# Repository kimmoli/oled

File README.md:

oled
====

LPC81X micro and OLED module interface.

Fits beneath LM096-128064 oled module.
datasheet e.g. http://s3.electrodragon.com/wp-content/uploads/2012/01/LM096-128064.pdf

Controller datasheet http://www.adafruit.com/datasheets/SSD1306.pdf

Pinheader has pins for I2C and UART0 (TTL) which is also used for ISP.
Supply voltage from 3.5 to 6.0 V (onboard 3.3V LDO)

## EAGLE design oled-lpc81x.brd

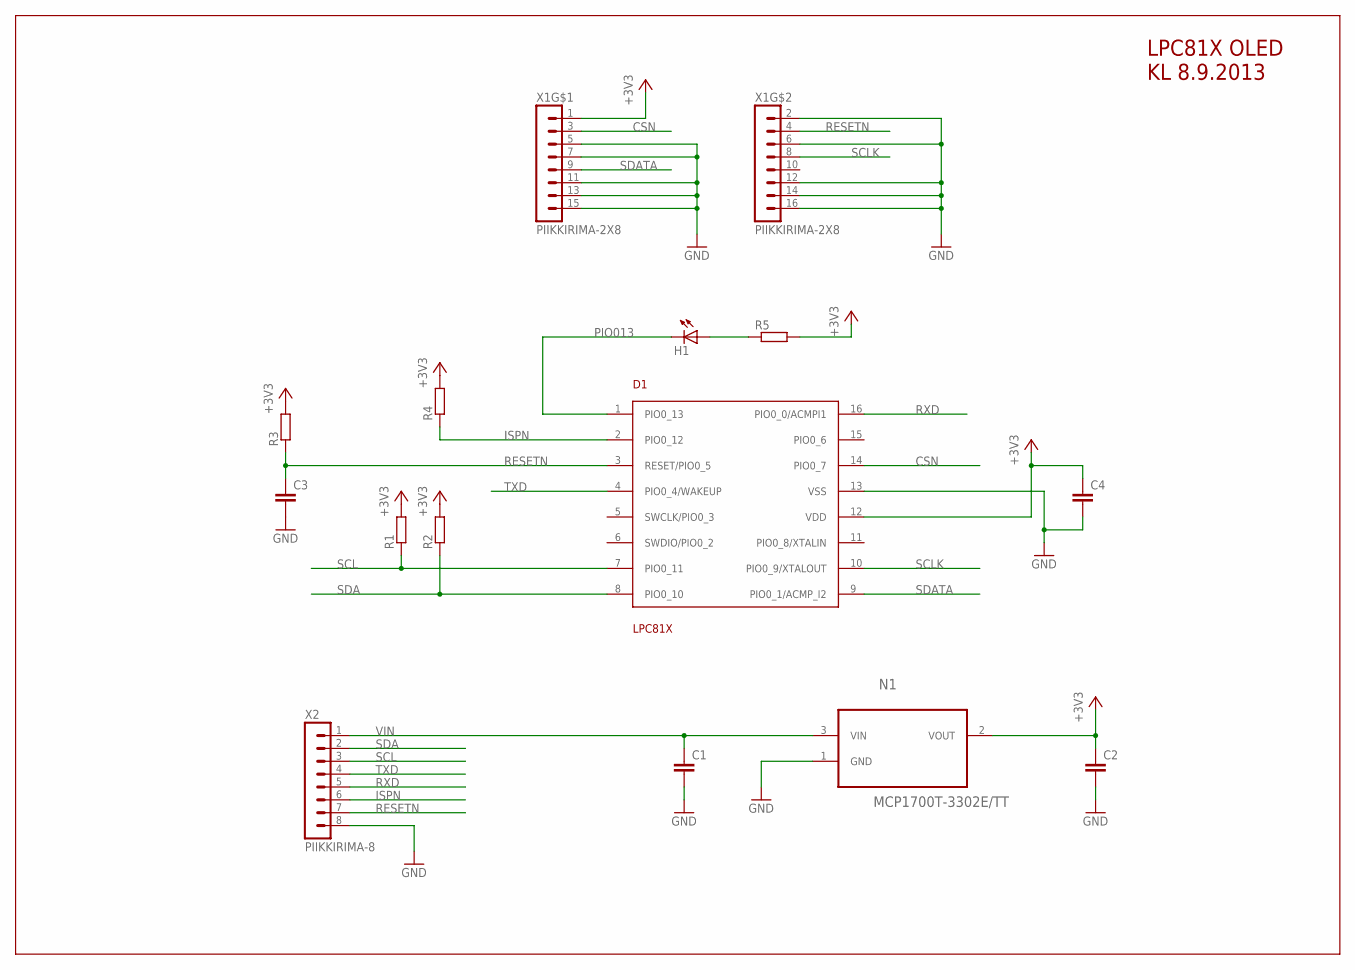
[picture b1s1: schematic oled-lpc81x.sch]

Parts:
C1, C2, C4: C-EUC0805; C0805
C3: C-EUC0603; C0603
D1: LPC81X; TSSOP16
H1: LEDCHIP-LED0603; CHIP-LED0603
N1: MCP1700T-3302E/TT; SOT95P237X112-3N
R1, R2, R3, R4, R5: R-EU_R0603; R0603
X1: PIIKKIRIMA-2X8
X2: PIIKKIRIMA-8

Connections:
+3V3: C2.1, C4.1, D1.12 (VDD), N1.2 (VOUT), R1.2, R2.2, R3.2, R4.2, R5.2, X1.1
CSN: D1.14 (PIO0_7), X1.3 (2)
GND: C1.2, C2.2, C3.2, C4.2, D1.13 (VSS), N1.1 (GND), X1.2 (1), X1.5 (3), X1.6 (3), X1.7 (4), X1.11 (6), X1.12 (6), X1.13 (7), X1.14 (7), X1.15 (8), X1.16 (8), X2.8
ISPN: D1.2 (PIO0_12), R4.1, X2.6
unnamed: H1.A, R5.1
PIO013: D1.1 (PIO0_13), H1.C
RESETN: C3.1, D1.3 (RESET/PIO0_5), R3.1, X1.4 (2), X2.7
RXD: D1.16 (PIO0_0/ACMPI1), X2.5
SCL: D1.7 (PIO0_11), R1.1, X2.3
SCLK: D1.10 (PIO0_9/XTALOUT), X1.8 (4)
SDA: D1.8 (PIO0_10), R2.1, X2.2
SDATA: D1.9 (PIO0_1/ACMP_I2), X1.9 (5)
TXD: D1.4 (PIO0_4/WAKEUP), X2.4
VIN: C1.1, N1.3 (VIN), X2.1

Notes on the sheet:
LPC81X OLED KL 8.9.2013

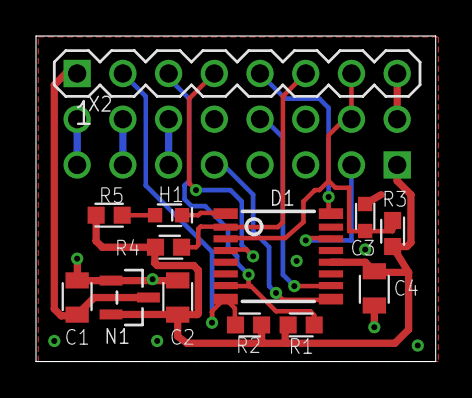
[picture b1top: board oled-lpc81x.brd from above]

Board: 2 copper layers, 22.2 x 18.1 mm, 14 parts (1 on the bottom side), 14 nets.

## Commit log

2013-09-08 Changed busses
    OLED now 3-wire SPI
    I2C external to header
2013-09-26 v2 - VDD/VSS connection to LPC812 corrected.
